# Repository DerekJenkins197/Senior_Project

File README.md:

# Senior_Project
A hub for file sharing and to centralize our software in one place.

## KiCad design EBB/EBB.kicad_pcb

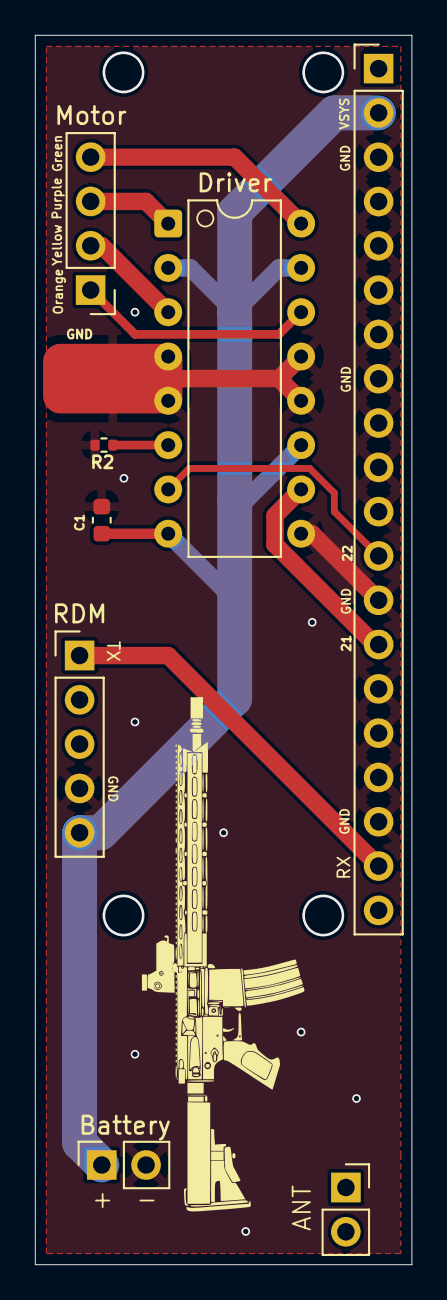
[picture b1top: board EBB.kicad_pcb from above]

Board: 2 copper layers, 21.6 x 70.5 mm, 8 parts (0 on the bottom side), 10 nets.

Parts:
Battery: Conn_01x02; PinSocket_1x02_P2.54mm_Vertical
C1: 100nF; C_0603_1608Metric
Driver: Motor_Driver; DIP-16_W7.62mm
GND: SolderWirePad_1x01_SMD_4x8mm
J6: Motor; PinHeader_1x04_P2.54mm_Vertical
Pico1: Conn_01x20_MountingPin; PinHeader_1x20_P2.54mm_Vertical
R2: 47K; R_0402_1005Metric
RDM: RDM Pins; PinHeader_1x05_P2.54mm_Vertical

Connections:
+5V: Battery.1, C1.1, Driver.2, Driver.8, Driver.11, Driver.15, Pico1.2, RDM.5
/GPIO_21: Driver.10, Pico1.14
/GPIO_22: Driver.7, Pico1.12
/Green: Driver.16, J6.4
/Orange: Driver.14, J6.1
/Purple: Driver.1, J6.3
/TX: Pico1.19, RDM.1
/Yellow: Driver.3, J6.2
GND: Battery.2, C1.2, Driver.4, Driver.5, Driver.9, Driver.12, Driver.13, GND.1, Pico1.3, Pico1.4, Pico1.5, Pico1.6, Pico1.7, Pico1.8, Pico1.9, Pico1.10, Pico1.11, Pico1.13, Pico1.15, Pico1.16, Pico1.17, Pico1.18, R2.1, RDM.4
unnamed: Driver.6, R2.2

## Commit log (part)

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2026-04-30 Added subsections for the differents aspects which will be considered.
2026-04-30 Added another section
2026-04-30 Updated page
2026-04-30 Fixed $s
2026-04-30 Fixed ' character
2026-04-30 Hopefully fixed the auto build issue.
2026-05-01 Added package to main
2026-05-01 Added Figure for FSD
2026-05-01 Changed references so that only used references are shown
2026-05-01 Changed some of the main page
2026-05-01 Added the Related Work and Solution/Contribution sections
2026-05-01 Added integration strategy body and fixed neal.bib which had a duplicate
2026-05-01 Added outline for project tasks section
2026-05-01 Add additional LaTeX output files to .gitignore
2026-05-01 Updated PDF
2026-05-01 Added Changes
2026-05-01 updated project tasks order
2026-05-01 Added Design Approach, Current Status, and Stretch Goals
2026-05-01 Lengthened Risk Assessment
2026-05-01 Fixed formatting error
2026-05-01 Updated main pdf
2026-05-02 Most sections complete
2026-05-02 Fixed Solution Space sentences
2026-05-02 Added firing control group image
2026-05-02 Removed the main files from the git cache
2026-05-02 Added a single citation to fig 1
2026-05-02 Many updates, close to final draft.
2026-05-02 Fixed citations
2026-05-02 Updated references with figures
